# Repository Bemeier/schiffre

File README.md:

# SCHIFFRE

The Schiffre project is a mechanical keyboard featuring a host board and shield design, using a Flexible Flat Cable (FFC) as interconnect.
All PCBs designed with Kicad 7.0. Case designed in Fusion.

## COMPONENTS
In this repository you will find everything to build a Schiffre 86 board.

- The host board: `schiffre_nrf`
- The shield PCB: `schiffre_86_pcb`
- The switch plate: `schiffre_86_plate`, with files for production from FR4.
- The case: `schiffre_86_case`, designed with both 3D printing and CNC machining in mind.

In addition there is a breakout board for the 30 pin FFC connector, with a RPi Pico header in `schiffre_pico`.

## BOM
See the production subfolders in the respective folders for the smd/assembly components.
Some additional components need to be ordered seperately.

**For the NRF host board (`schiffre_nrf`):**
 - One E73-2G4M08S1C bluetooth module [AliExpress](https://aliexpress.com/item/32944356249.html)
 - One 100mm reversible FFC calbe with 30 pins and .5mm pitch [AliExpress](https://aliexpress.com/item/1005002259855390.html) to connect between the host and shield pcb (`schiffre_86_pcb`).
 - A LiPo rechargable battery. There is room for a long, but narrow and thin one.
   - Thickness <= 4mm, and width <= 25mm. 
   - Make sure to only use LiPos with battery protection ICs included (usually the case).
   - 4x20x60mm 600mAh [AliExpress](https://aliexpress.com/item/1005005086965061.html)
   - 4x25x100mm 1200mAh [AliExpress](https://aliexpress.com/item/1005005067026996.html)

**For the Case (`schiffre_86_case`):**
 - M3x5.7x4.6 and M2x4x3.6 Heat-set inserts (if 3D printing the case or machining from plastics) [AliExpress](https://www.aliexpress.com/item/4001258499799.html).
 - DIN912 socket head screws: 8x M3x10mm, 4x M2x6mm [AliExpress](https://www.aliexpress.com/item/32810872544.html)
 - Plate mounting gaskets and case feet need to be 3D printed from TPU.

## FIRST BUILD
Below some pictures of the first build in progress.
PCBs from JLCPCB, case 3D printed from PETG.

## LAYOUTS
The schiffre86 supports both ANSI and ISO (Enter, split left shift) layouts, split backspace, and split spacebars.
See the [keyboard layout editor](http://www.keyboard-layout-editor.com/#/gists/19b67d0e8a5331e922c6eb11a3dd6522) for details.

## FIRMWARE
ZMK support works. See the [schiffre branch on our zmk fork](https://github.com/Bemeier/zmk/tree/schiffre). 
There is a [zmk-config template for the schiffre86](https://github.com/Bemeier/schiffre86-zmk-config) that you can clone to build your own keymap.
It comes with support for nickcoutsos' [keymap-editor](https://nickcoutsos.github.io/keymap-editor/).

For a precompiled version see `schiffre86-schiffre_nrf-zmk.uf2` in the `firmware` folder.

For instructions on how to setup flashing the modules, refer to Joric's excellent [nrfmicro wiki](https://github.com/joric/nrfmicro/wiki/).
The main thing to do is to [flash the bootloader](https://github.com/joric/nrfmicro/wiki/Bootloader) onto the E73 modules.

## PROJECT NAME
*Schiffre* is a combination of the german word *Chiffre* (translation of Cypher, the board this project was based on originally), and the word *Schiff*, which means ship or big boat, reflecting the shape of the keyboard.

## TODO
 - Couldn't get the XTAL to work yet
 - Add some decoupling caps..
 - Add a Battery switch
 - Test the external power for backlight / LEDs.
 - Revisit the FCC pinout, especially with other aux devices that may be on the shield board (i.e. encoders or OLEDs)
 - Make FCC "reversible" i.e. mirror power pins.

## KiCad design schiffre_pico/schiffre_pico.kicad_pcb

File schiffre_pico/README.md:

# SCHIFFRE PICO

A Raspberry Pi Pico RP2040 compatible host board implementing the 30 pin Flexible Flat Cable interconnect.
This was mainly designed as a breakout board for the 30 pin connector.
This may be changed in the future to feature a form factor more suitable for integration in a case.

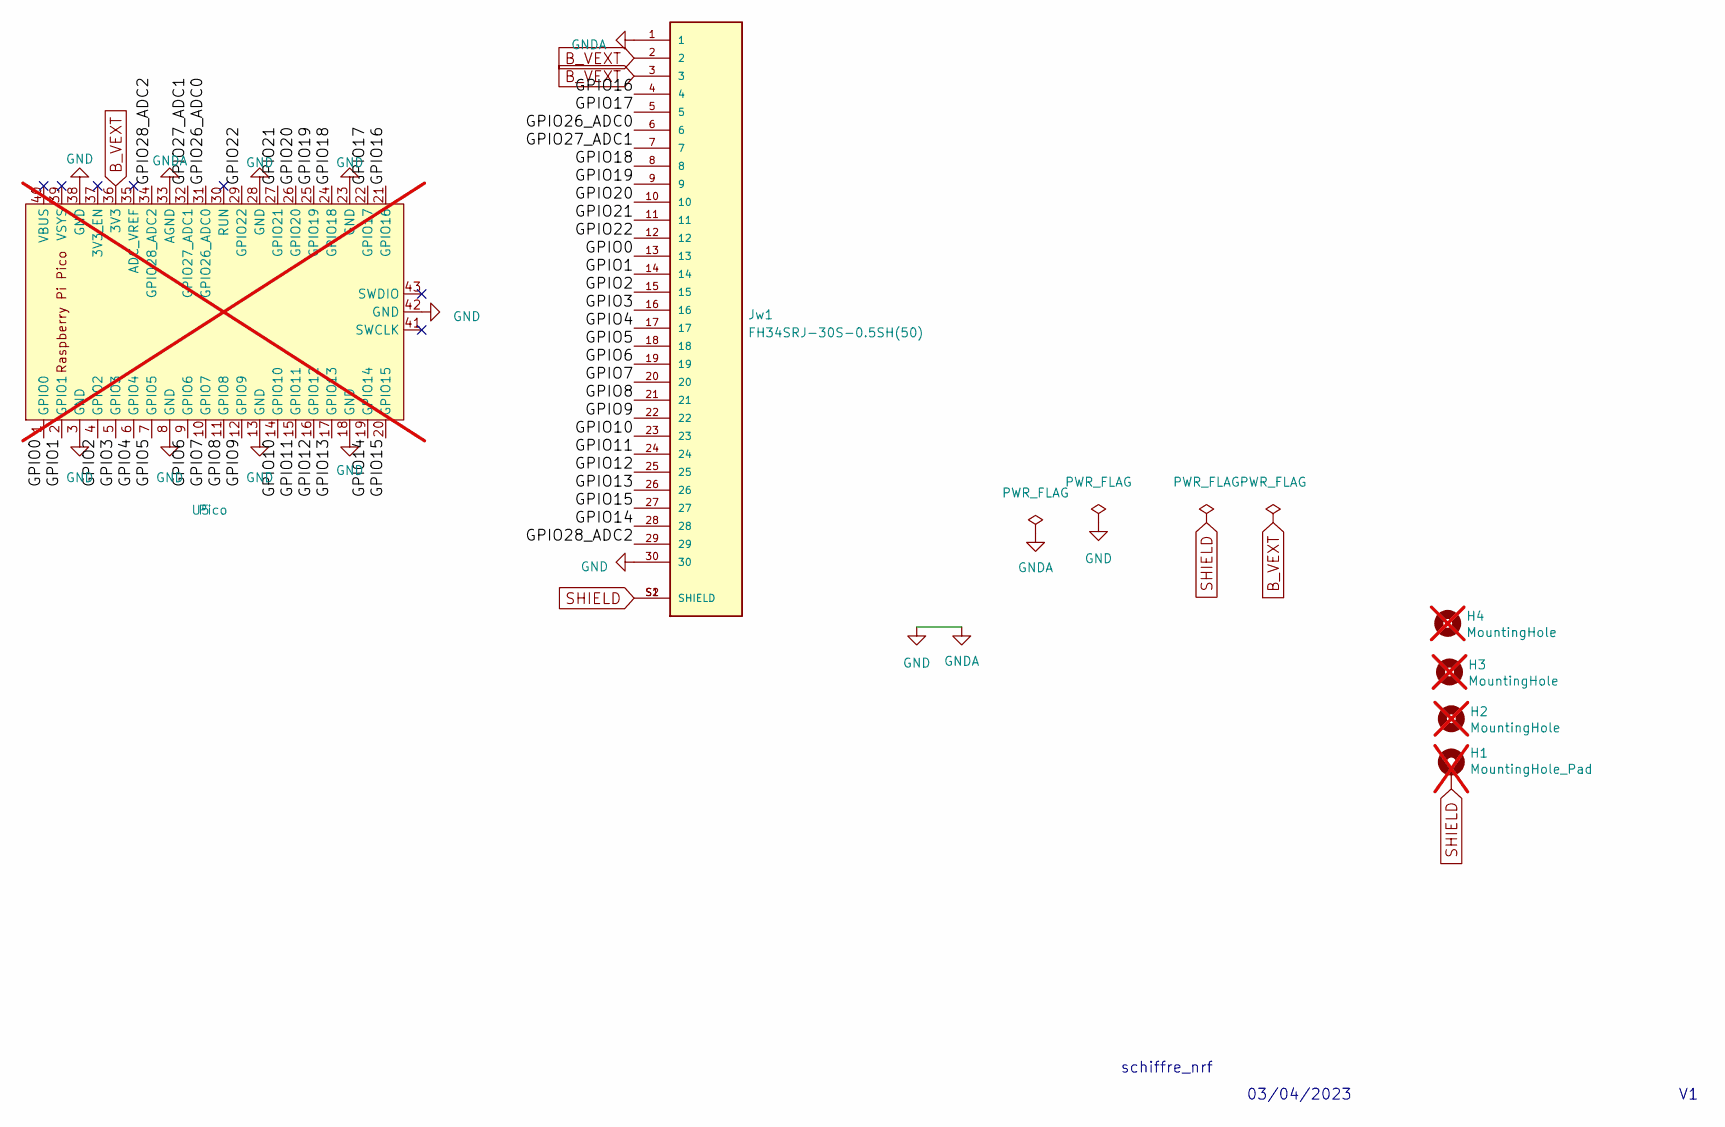
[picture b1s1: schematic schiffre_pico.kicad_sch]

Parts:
H1: MountingHole_Pad; MountingHole_2.2mm_M2_DIN965_Pad_TopBottom; not fitted
H2, H3, H4: MountingHole; MountingHole_2.2mm_M2_DIN965; not fitted
Jw1: FH34SRJ-30S-0.5SH(50); HRS_FH34SRJ-30S-0.5SH(50); PARTREV 1; JLCPART C324727
U5: Pico; RPi_Pico_SMD_TH; not fitted

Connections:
/GPIO0: Jw1.13, U5.1 (GPIO0)
/GPIO1: Jw1.14, U5.2 (GPIO1)
/GPIO2: Jw1.15, U5.4 (GPIO2)
/GPIO3: Jw1.16, U5.5 (GPIO3)
/GPIO4: Jw1.17, U5.6 (GPIO4)
/GPIO5: Jw1.18, U5.7 (GPIO5)
/GPIO6: Jw1.19, U5.9 (GPIO6)
/GPIO7: Jw1.20, U5.10 (GPIO7)
/GPIO8: Jw1.21, U5.11 (GPIO8)
/GPIO9: Jw1.22, U5.12 (GPIO9)
/GPIO10: Jw1.23, U5.14 (GPIO10)
/GPIO11: Jw1.24, U5.15 (GPIO11)
/GPIO12: Jw1.25, U5.16 (GPIO12)
/GPIO13: Jw1.26, U5.17 (GPIO13)
/GPIO14: Jw1.28, U5.19 (GPIO14)
/GPIO15: Jw1.27, U5.20 (GPIO15)
/GPIO16: Jw1.4, U5.21 (GPIO16)
/GPIO17: Jw1.5, U5.22 (GPIO17)
/GPIO18: Jw1.8, U5.24 (GPIO18)
/GPIO19: Jw1.9, U5.25 (GPIO19)
/GPIO20: Jw1.10, U5.26 (GPIO20)
/GPIO21: Jw1.11, U5.27 (GPIO21)
/GPIO22: Jw1.12, U5.29 (GPIO22)
/GPIO26_ADC0: Jw1.6, U5.31 (GPIO26_ADC0)
/GPIO27_ADC1: Jw1.7, U5.32 (GPIO27_ADC1)
/GPIO28_ADC2: Jw1.29, U5.34 (GPIO28_ADC2)
B_VEXT: Jw1.2, Jw1.3, U5.36 (3V3)
GND: Jw1.1, Jw1.30, U5.3 (GND), U5.8 (GND), U5.13 (GND), U5.18 (GND), U5.23 (GND), U5.28 (GND), U5.33 (AGND), U5.38 (GND), U5.42 (GND)
SHIELD: H1.1, Jw1.S1 (SHIELD), Jw1.S2 (SHIELD)

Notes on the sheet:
03/04/2023
schiffre_nrf

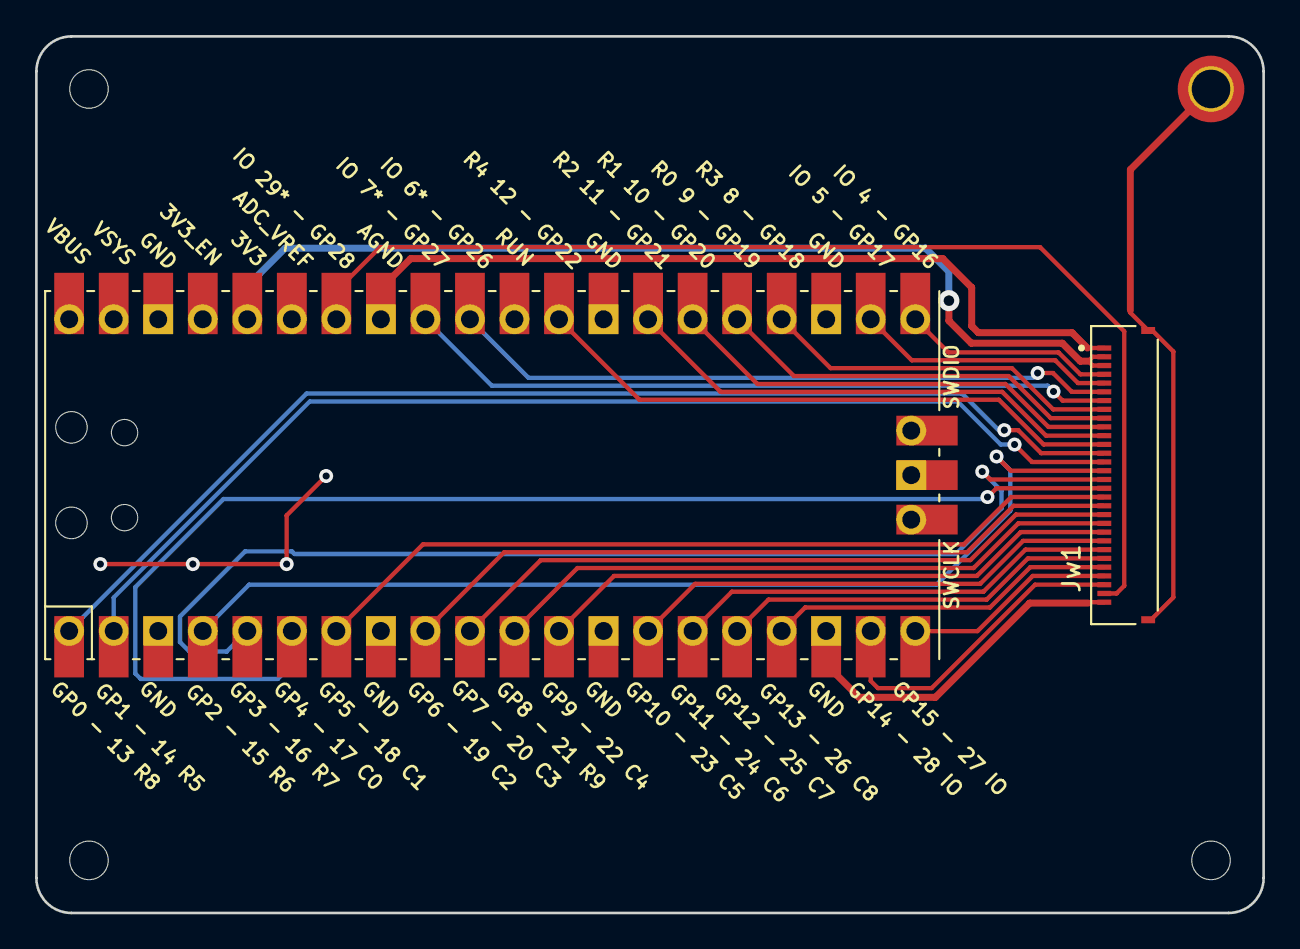
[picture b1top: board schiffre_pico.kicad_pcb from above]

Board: 2 copper layers, 70.0 x 50.0 mm, 6 parts (0 on the bottom side), 29 nets.

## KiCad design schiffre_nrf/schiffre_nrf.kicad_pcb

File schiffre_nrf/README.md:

# SCHIFFRE NRF

An NRF52840 based host board for USB & BLE connected Keyboards featuring a Flexible Flat Cable interconnect.

## Credits
This board is heavily based on [joric's nrfmicro](https://github.com/joric/nrfmicro).
USB/ESD Protection taken from the [UDB-S project](https://github.com/Unified-Daughterboard/UDB-S).

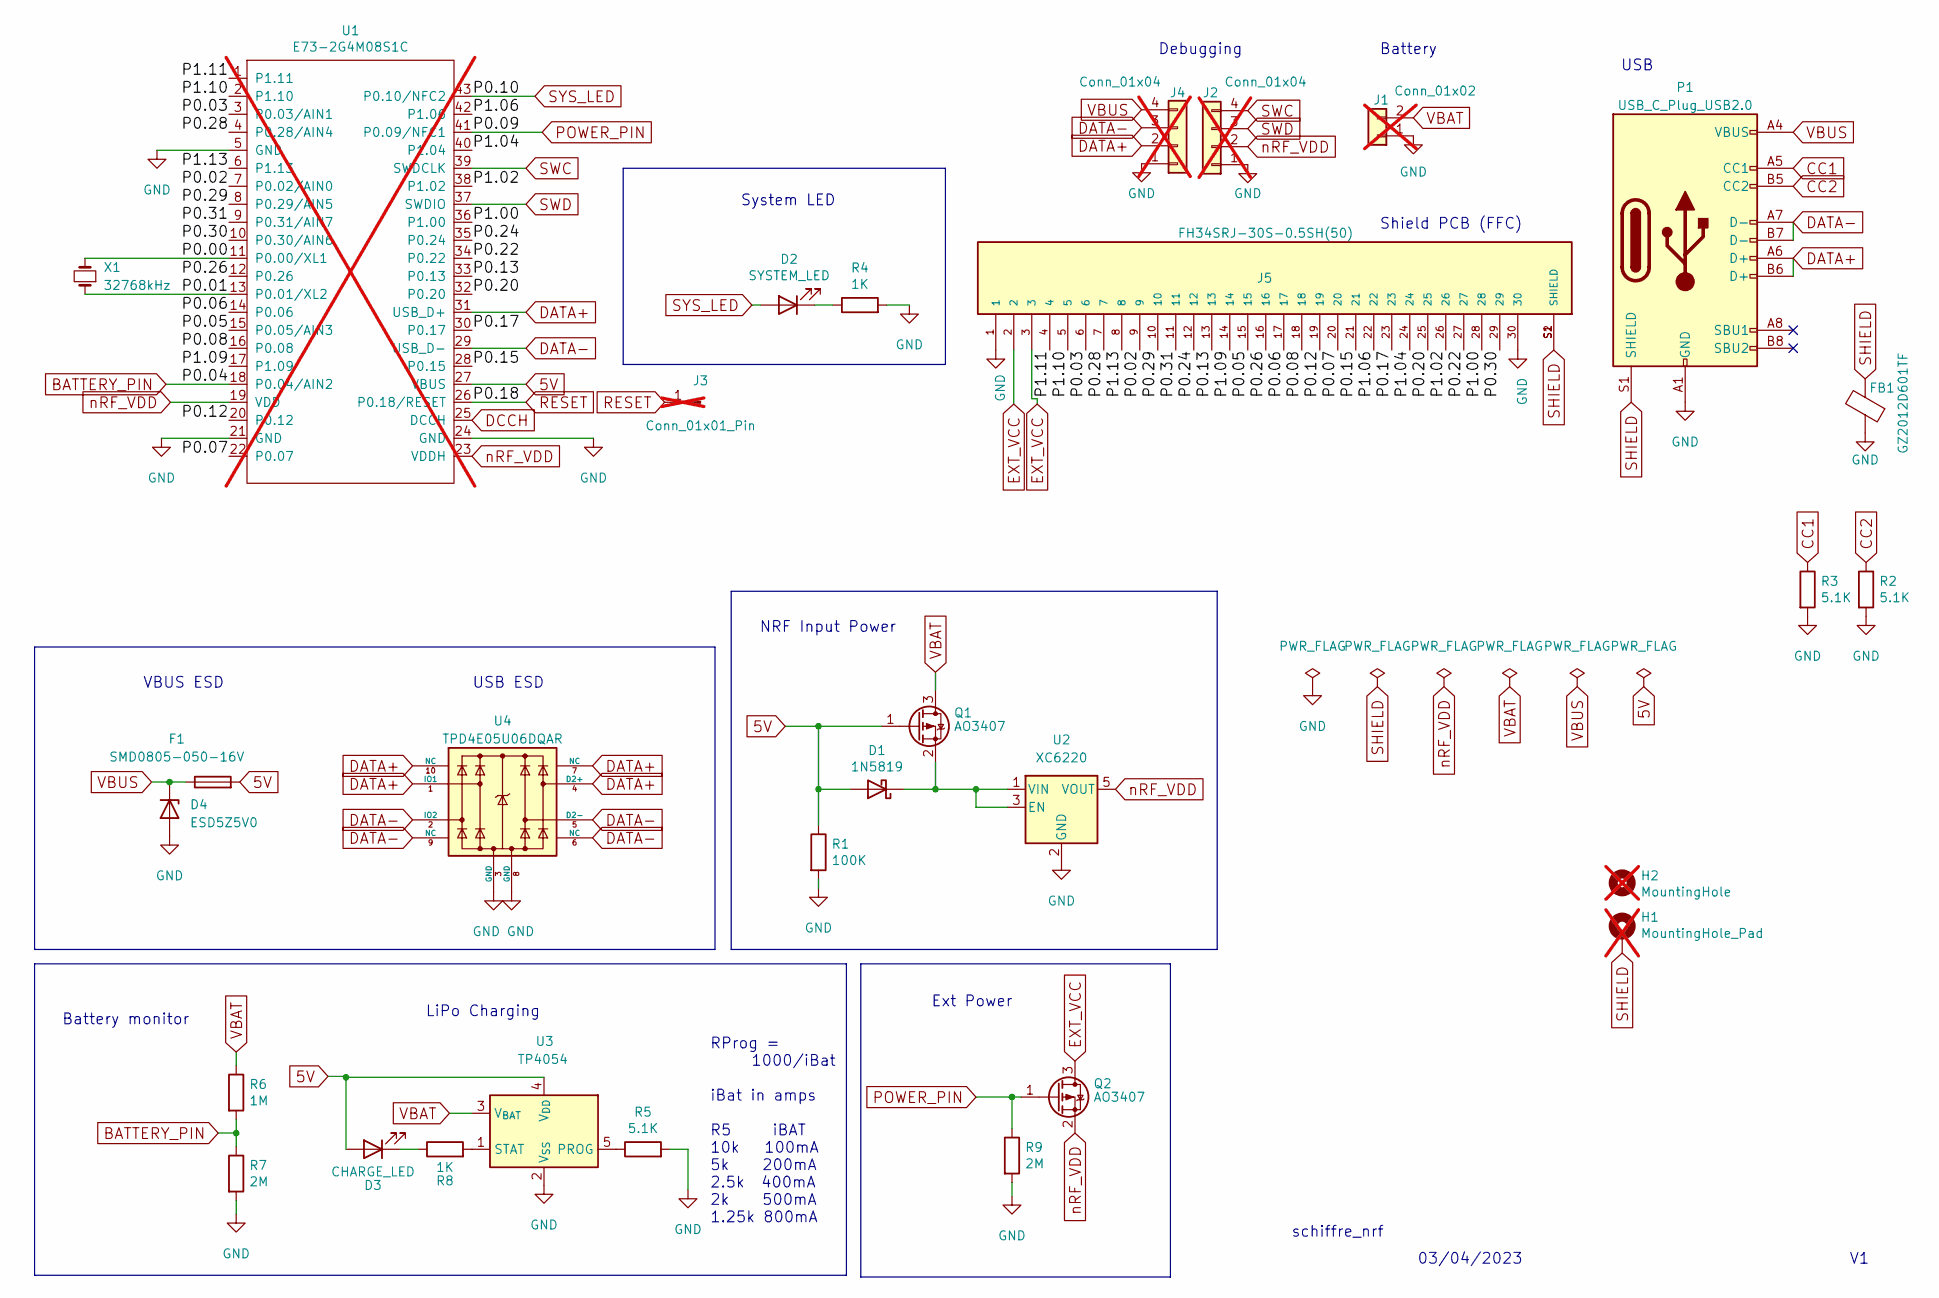
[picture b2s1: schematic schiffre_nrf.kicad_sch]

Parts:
D1: 1N5819; D_SOD-323F; MPN C191023
D2: SYSTEM_LED; LED_0603_1608Metric; MPN C2290
D3: CHARGE_LED; LED_0603_1608Metric; MPN C2286
D4: ESD5Z5V0; D_SOD-523; MPN C727161
F1: SMD0805-050-16V; Fuse_0805_2012Metric; MPN C2833485
FB1: GZ2012D601TF; L_0805_2012Metric; MPN C1017
H1: MountingHole_Pad; MountingHole_2.2mm_M2_DIN965_Pad_TopBottom; not fitted
H2: MountingHole; MountingHole_2.2mm_M2_DIN965; not fitted
J1: Conn_01x02; SolderWire-0.15sqmm_1x02_P4mm_D0.5mm_OD1.5mm; not fitted
J2, J4: Conn_01x04; PinSocket_1x04_P2.54mm_Vertical; not fitted
J3: Conn_01x01_Pin; PinHeader_1x01_P1.00mm_Vertical; not fitted
J5: FH34SRJ-30S-0.5SH(50); HRS_FH34SRJ-30S-0.5SH(50); PARTREV 1; JLCPART C324727
P1: USB_C_Plug_USB2.0; USB_C_Receptacle_Palconn_UTC16-G_3D; MPN C709357; JLCPART C709357
Q1, Q2: AO3407; SOT-23; MPN C351408
R1: 100K; R_0603_1608Metric; MPN C25803
R2, R3, R5: 5.1K; R_0402_1005Metric; MPN C25905
R4, R8: 1K; R_0402_1005Metric; MPN C11702
R6: 1M; R_0603_1608Metric; MPN C22935
R7, R9: 2M; R_0603_1608Metric; MPN C22976
U1: E73-2G4M08S1C; E73-2G4M08S1C-52840; not fitted
U2: XC6220; SOT-23-5; MPN C86534
U3: TP4054; SOT-23-5; MPN C32574
U4: TPD4E05U06DQAR; USON-10_2.5x1.0mm_P0.5mm; Manufacturer Part # TPD4E05U06DQAR; LCSC Part # C138714
X1: 32768kHz; Crystal_SMD_3215-2Pin_3.2x1.5mm; MPN C32346

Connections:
5V: D1.2 (A), D3.2 (A), F1.2, Q1.1 (G), R1.1, U1.27 (VBUS), U3.4 (V_{DD})
/P0.00: U1.11 (P0.00/XL1), X1.2
/P0.01: U1.13 (P0.01/XL2), X1.1
/P0.02: J5.9, U1.7 (P0.02/AIN0)
/P0.03: J5.6, U1.3 (P0.03/AIN1)
/P0.05: J5.15, U1.15 (P0.05/AIN3)
/P0.06: J5.17, U1.14 (P0.06)
/P0.07: J5.20, U1.22 (P0.07)
/P0.08: J5.18, U1.16 (P0.08)
/P0.12: J5.19, U1.20 (P0.12)
/P0.13: J5.13, U1.33 (P0.13)
/P0.15: J5.21, U1.28 (P0.15)
/P0.17: J5.23, U1.30 (P0.17)
/P0.20: J5.25, U1.32 (P0.20)
/P0.22: J5.27, U1.34 (P0.22)
/P0.24: J5.12, U1.35 (P0.24)
/P0.26: J5.16, U1.12 (P0.26)
/P0.28: J5.7, U1.4 (P0.28/AIN4)
/P0.29: J5.10, U1.8 (P0.29/AIN5)
/P0.30: J5.29, U1.10 (P0.30/AIN6)
/P0.31: J5.11, U1.9 (P0.31/AIN7)
/P1.00: J5.28, U1.36 (P1.00)
/P1.02: J5.26, U1.38 (P1.02)
/P1.04: J5.24, U1.40 (P1.04)
/P1.06: J5.22, U1.42 (P1.06)
/P1.09: J5.14, U1.17 (P1.09)
/P1.10: J5.5, U1.2 (P1.10)
/P1.11: J5.4, U1.1 (P1.11)
/P1.13: J5.8, U1.6 (P1.13)
BATTERY_PIN: R6.2, R7.1, U1.18 (P0.04/AIN2)
CC1: P1.A5 (CC1), R3.1
CC2: P1.B5 (CC2), R2.1
DATA+: J4.2, P1.A6 (D+), P1.B6 (D+), U1.31 (USB_D+), U4.1 (IO1), U4.4 (D2+), U4.7 (NC), U4.10 (NC)
DATA-: J4.3, P1.A7 (D-), P1.B7 (D-), U1.29 (USB_D-), U4.2 (IO2), U4.5 (D2-), U4.6 (NC), U4.9 (NC)
DCCH: U1.25 (DCCH)
EXT_VCC: J5.2, J5.3, Q2.3 (D)
GND: D4.2 (A), FB1.1, J1.1, J2.1, J4.1, J5.1, J5.30, P1.A1 (GND), P1.A12 (GND), P1.B1 (GND), P1.B12 (GND), R1.2, R2.2, R3.2, R4.2, R5.2, R7.2, R9.2, U1.5 (GND), U1.21 (GND), U1.24 (GND), U2.2 (GND), U3.2 (V_{SS}), U4.3 (GND), U4.8 (GND)
unnamed: D1.1 (K), Q1.2 (S), U2.1 (VIN), U2.3 (EN)
unnamed: D2.1 (K), R4.1
unnamed: D3.1 (K), R8.1
unnamed: R5.1, U3.5 (PROG)
unnamed: R8.2, U3.1 (STAT)
POWER_PIN: Q2.1 (G), R9.1, U1.41 (P0.09/NFC1)
RESET: J3.1, U1.26 (P0.18/RESET)
SHIELD: FB1.2, H1.1, J5.S1 (SHIELD), J5.S2 (SHIELD), P1.S1 (SHIELD)
SWC: J2.4, U1.39 (SWDCLK)
SWD: J2.3, U1.37 (SWDIO)
SYS_LED: D2.2 (A), U1.43 (P0.10/NFC2)
VBAT: J1.2, Q1.3 (D), R6.1, U3.3 (V_{BAT})
VBUS: D4.1 (K), F1.1, J4.4, P1.A4 (VBUS), P1.A9 (VBUS), P1.B4 (VBUS), P1.B9 (VBUS)
nRF_VDD: J2.2, Q2.2 (S), U1.19 (VDD), U1.23 (VDDH), U2.5 (VOUT)

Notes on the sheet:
LiPo Charging
03/04/2023
VBUS ESD
RProg = 1000/iBat iBat in amps R5 iBAT 10k 100mA 5k 200mA 2.5k 400mA 2k 500mA 1.25k 800mA
Debugging
USB
NRF Input Power
schiffre_nrf
USB ESD
System LED
Shield PCB (FFC)
Battery monitor
Battery
Ext Power

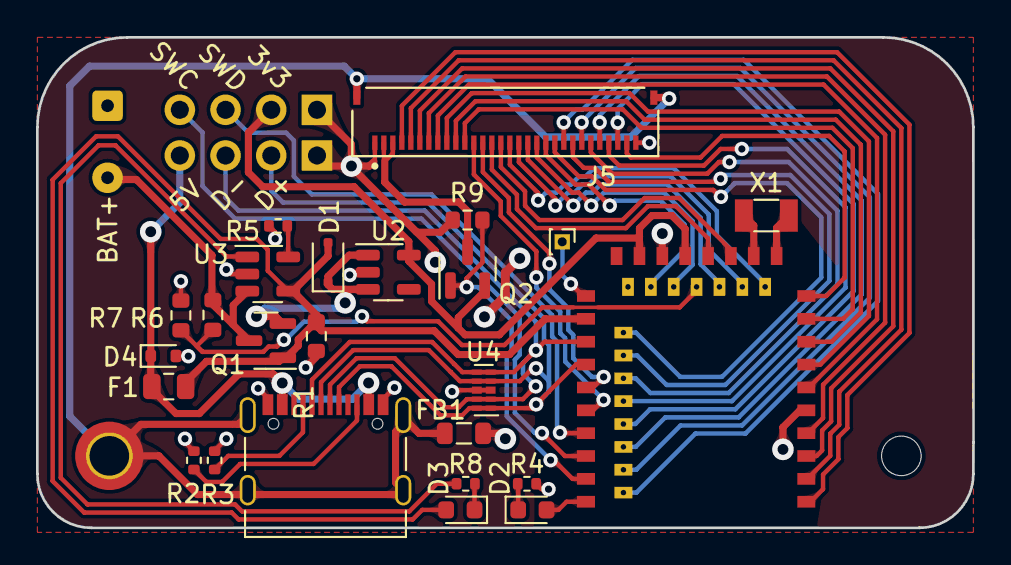
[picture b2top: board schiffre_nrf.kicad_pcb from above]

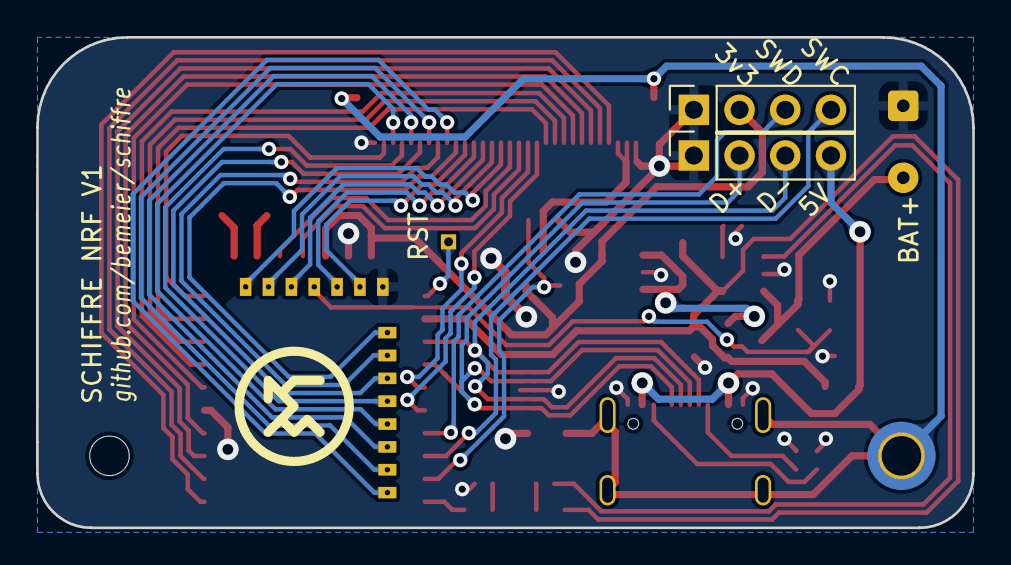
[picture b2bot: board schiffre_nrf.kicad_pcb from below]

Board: 2 copper layers, 52.0 x 27.2 mm, 30 parts (3 on the bottom side), 50 nets.

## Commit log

2023-03-04 Initial commit. First version of PCBs that went into production.
2023-03-06 factored out the pico breakout board
2023-03-06 update components
2023-03-06 small drc things
2023-03-09 reference firmware dev
2023-03-19 add firmware info
2023-03-19 added case files
2023-03-19 readme case
2023-03-19 firmware instructions
2023-03-19 update img
2023-03-19 Layouts
2023-03-19 pictures of first prototype
